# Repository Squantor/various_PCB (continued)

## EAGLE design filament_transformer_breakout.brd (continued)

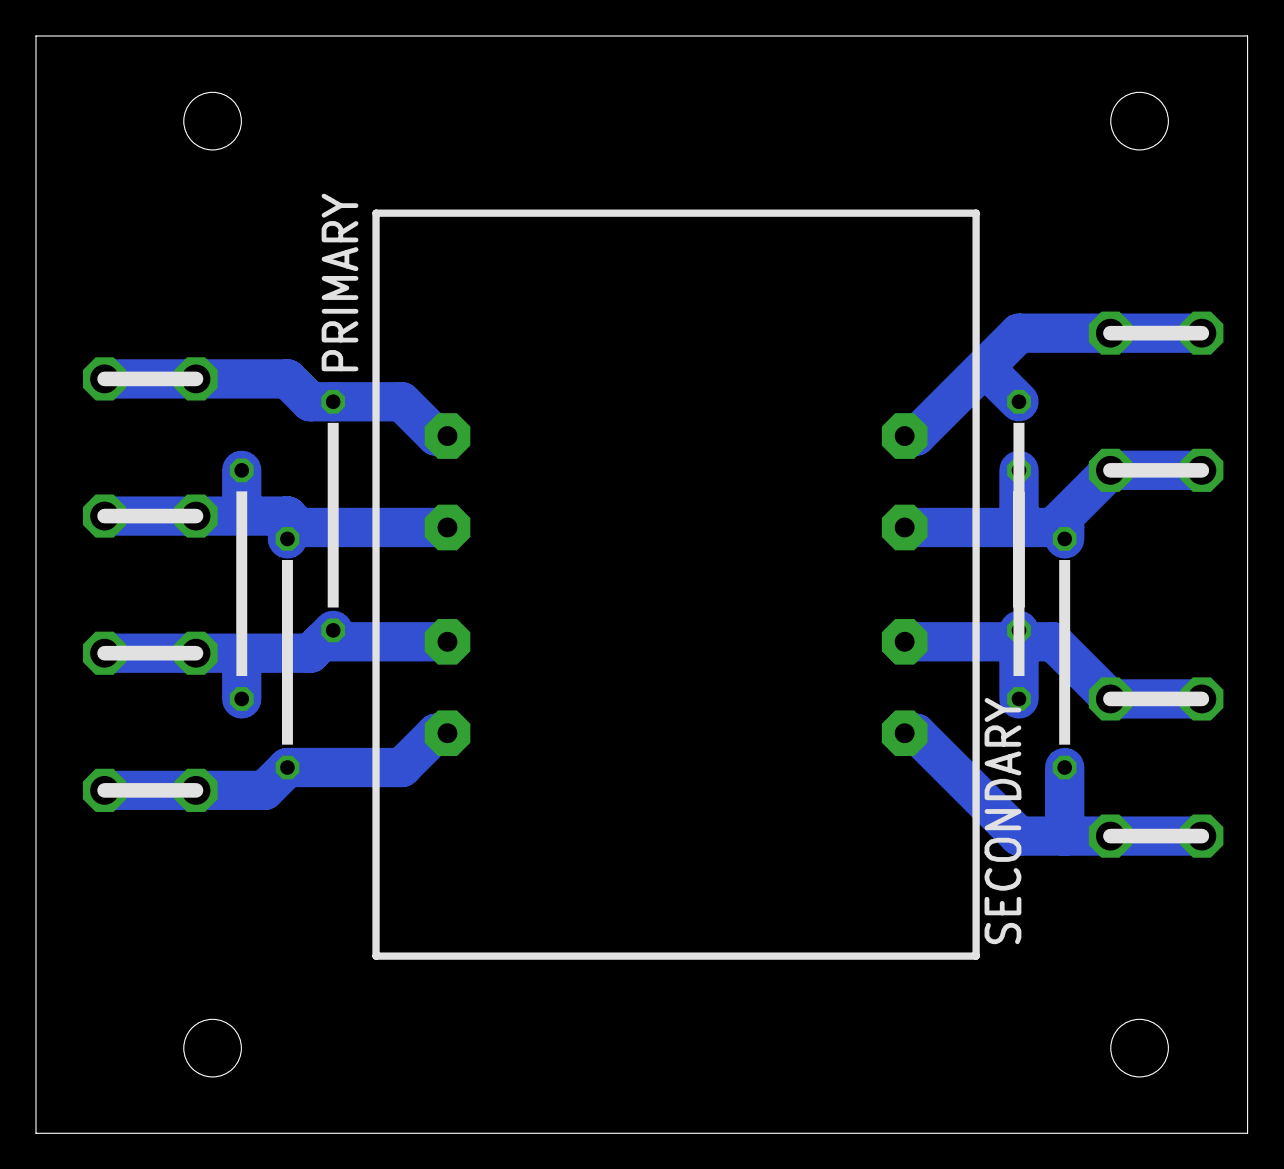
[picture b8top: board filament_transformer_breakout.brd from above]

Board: 2 copper layers, 67.3 x 61.0 mm, 15 parts (0 on the bottom side), 8 nets.

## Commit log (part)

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2021-03-21 forgot footprint definition for inductor
2021-03-21 placed and routed
2021-03-21 reviewed little logic SOT353 PCB
2021-03-21 reviewed SSR module
2021-04-01 WIP readme update
2021-04-01 further expanded readme and documentation
2021-04-01 fixed incorrect link to picture
2021-04-01 added frequencies to example table
2021-04-14 changed boostcap size, changed high current path to use multiple smaller vias
2021-04-16 different SSR's needed
2021-04-17 optimized placement of components to be more compact
2021-04-17 updated high power SSR with more compact components
2021-04-17 routed more compact components
2021-04-17 silk changes
2021-04-17 started with SY8291ABC breakout
2021-04-17 modified, layedout, and completed, now wait one day in between
2021-04-18 added additional current label, optimized some track placement
2021-04-18 added type of SSR label, fixed incorrect resistor value, updated versionnumber
2021-04-18 changed name of optotriac to generic name, the type field will tell what type of SSR it is
2021-04-18 updated versionnumber, changed optotriac name, added SSR type label, added cutouts near mounting holes and pins at potential
2021-04-19 updated versionnumber, removed one input capacitor, made design more compact, removed solder mask under IC for better cooling, added PCB title, changed Vout label
2021-04-19 updated versionnumber, fixed DRC errors
2021-04-19 added soldermask keepout, DRC errors fixed, title added, changed Vout Iout labels
2021-04-20 updated versionnumber, changed copper planes to have bigger spacing values, optimized ground planes a bit
2021-04-21 changed indicator power led, changed inductor size, enlarged PCB a bit
2021-04-22 updated versionnumber, changed coil sizes
2021-04-22 updated versionnumbers, added pin labels
2021-04-22 updated coil size, some component position optimizations
2021-04-23 changed some trace positions to have more distance from other potentials
2021-04-23 updated versionnumber, minor silk changes
2021-04-23 added current label, minor silk moves
2021-04-23 am forgot component labeling
2021-04-24 added picture of the CH340E module
2021-06-07 added initial USB-C PD only breakout
2021-06-07 updated with some USB-C connectors
2021-06-08 added LED indicator and breakout connector
2021-06-08 updated library with fixed USB-C PD connector
2021-06-08 ERC passed
2021-06-08 changed pin assignment on breakout to ease routing
2021-06-08 added additional 5mm led
2021-06-08 routed all the traces
2021-06-09 added on PCB USB-C connector
2021-06-09 changed LED series resistor to 0603
2021-06-09 copied over USB-C PD only breakout to new project
2021-06-09 changed USB-C connector
2021-06-10 minor copper changes, added pin labels
2021-06-10 added breakout, testpins, updated TODO's
2021-06-10 routed and silk placement completed
2021-06-10 started with CH340E with USB-C module
2021-06-10 placement fixed with on PCB USB-C breakout
2021-06-10 added regulator, changed resistor assignments
2021-06-11 created usb-C filter
2021-06-11 updated usb output schematic symbol
2021-06-12 updated versionnumber
2021-06-12 updated versionnumber, usb data lines routing improved, led position and test pads updated
2021-06-12 updated versionnumber, optimized differential pairs, silk placement improved
2021-06-12 updated todo, updated versionnumber
2021-06-12 silk and led position optimization
2021-06-12 seems that I actually worked on the CH340B USB breakout
2021-06-12 changed to CH340E and started routing/layout
2021-06-13 changed regulator to SOT23 lower cost regulator, updated versionnumber, put versionnumber and mechanical in seperate box
2021-06-13 added box
2021-06-13 routed SOT-23 regulator
2021-06-13 updated versionnumber, silk movement
2021-06-13 updated versionnumber, optimized some component placement
2021-06-13 updated versionnumber, added additional led to show usb output power, added jumper to separate the two power domains, changed led positioning
2021-06-13 renaming project names, seem they kept their origin project names!
2021-06-29 added USB-C breakout box 3d model as a copy from the hammond 1551M
2021-07-01 added USB-C hole to the box
2021-07-02 added opening for header connectors
2021-09-05 fixed usb A out schematic symbol
2021-09-05 updated versionnumber, fixed schematic component, some changes here and there on PCB
2021-09-05 bus link jumper to 0805 size due to higher currents
2021-09-05 routed and fixed error in board
2021-09-13 started sharp memory LCD breakout
2021-09-13 started with low power oscillator test
2021-09-13 initial schematic
2021-09-14 WIP schematic
2021-09-24 initial schematic with just connections
2021-09-24 started with inital layout
2021-09-25 added stabistor
2021-09-25 small changes
2021-09-26 added crystal footprint, passing ERC, updated versionnumber
2021-09-26 placing, routing, added decoupling capacitor, placing silk
2021-09-27 added TODO's
2021-09-27 added extra ground plane to PCB, added REG710 step up converter
2021-09-27 forgot resistor footprint
2021-09-28 changed regulator setup, updated versionnumber
2021-09-28 moved pinning of board, placed, and routed everything
2021-09-28 added extra ground testpoint near signal for easy measurements
2021-09-29 trying to add a TVS diode
2021-09-30 placed and routed TVS diode array, updated silk
2021-09-30 fixed mistake, missing resistor on DISP
2021-10-01 final checks before production
2021-10-01 final check before production
2021-10-12 minor silk changes
2021-10-12 updated version number and TODO
2021-10-12 few extra gnd vias
2021-10-12 changed one component value label to align better
2021-10-13 started with breakout for kailh choc buttons
2021-10-13 created keymatrix and initial placement
2021-10-15 modified keypad demo with simple pins
2021-10-15 added additional diode footprints
2021-10-15 routing completed, changed pinout to ease routing
2021-10-15 silk placement completed
2021-10-15 updated BOM
2021-10-15 started with 3 switch kailh breakout
2021-10-15 newer PCB library
2021-10-15 work in progress on schematic of 3 button kailh choc button breakout
2021-10-15 started with 4 switch kailh choc frontplate
2021-10-15 finished PCB
2021-10-15 copied 4 switch plate to 3 switch
2021-10-16 imported plate PCB to make sure we have the same dimensions
2021-10-16 routed and placed silk
2021-10-18 resizing PCB and different mounting method
2021-10-18 changed hole plate to smaller PCB so it can be tiled
2021-10-19 updated physical dimensions for 3 button choc frontplate
2021-10-19 moved connectors
2021-10-19 changed connector positions
2021-11-02 updated library
2021-11-03 place&route&silk position completed
2021-11-03 updated status
2021-11-07 schematic and routing completed
2021-11-07 renamed SOT363 breakout, as SOT is an abbreviation after all
2021-11-07 started with SOT457 breakout
2021-11-07 completed SOT457 breakout
2021-11-07 updated design status
2021-11-10 parking SOT666 breakout, not producable by oshpark
2021-11-10 moved some traces
2021-11-15 removed unproducable by oshpark project
2022-02-16 changed JST connectors to edge connectors, changed switch pitch
2022-02-16 updated 4 button breakout kailh switches
2022-03-22 added breakout for polulu 16 pin stepper motor driver
2022-03-22 further updates to breakout
2022-04-20 started with netfilter module
2022-04-21 assigned footprints from new PCB library
2022-04-21 added wurth library
2022-07-18 added test mainboard for a 10*10cm aluminium box
2022-07-18 added kicad6 ignorables
2022-07-18 inital mainboard test layout
2022-07-24 further connector placement
2022-07-25 further routing of busses, but blocked now
2022-08-29 updated footprints, silk placements
2022-09-16 alubox mainboard
2022-09-23 created board raspberry pi pico SWD breakout
2022-09-23 changed connector so we have silk space for versionnumber and date code
2022-09-23 updated to have power LED, silk placement, board layouted
2022-11-28 started with the SG1 strapubox template
2022-11-28 WIP schematic entry and component+footprint definitions
2022-11-29 WIP rectifier section
2022-11-30 WIP further development
2022-12-01 routing completed WIP silk placement
2023-02-11 updated cutout sizes
2023-02-11 added mounting hole definitions (forgot to add
2023-02-11 added small fixes, through wire holes
2023-04-09 redid board but with proper hole spacing and more flexible sizing
2023-04-09 fixed ERC errors
2023-04-10 WIP adding front LED and power switches
2023-04-11 further updates and additions to switch and leds
2023-04-14 place and route LED and switches
2023-04-15 fixed error with power switch pinout
2023-04-16 further routing
2023-04-17 updated pinouts
2023-04-18 routed new voltage rails
2023-05-05 started with alubox powersupply
2023-05-05 fixed board outline
2023-05-05 updated schematic with lessons learned
2023-05-05 forgot to save schematic
2023-05-05 minor positioning
2023-05-07 small outline adjustment to fit adapter box better
2023-05-13 added input switching connectors
2023-05-13 further changes of decoupling of AC inputs
2023-05-14 WIP PSU circuits
2023-05-19 further added PSU parts and fixed output regulator
2023-05-19 minor schematic fixes and errors
2023-05-19 further net shifts, changing component footprints to better fit
2023-05-19 WIP placing parts around regulators
2023-05-21 WIP component placement
2023-05-21 fixed power supply rail names
2023-05-23 Routing completed, WIP silk placement
2023-05-23 WIP silk placement
2023-05-27 reorganizing schematic
2023-05-27 added small regions for diodes to cool
2023-05-27 ERC passes, added powerflags
2023-05-27 fixed DRC errors
2023-05-28 changed jack connectors to use holed jacks
2023-05-28 minor optimizations
2023-05-28 placed and routed capacitors
2023-05-28 fixed small issue that aisler reported
2023-05-30 fixed aisler problems
2023-06-13 added 10x10 alubox drillguide
2023-06-19 added pin labels
2023-06-30 updated to kicad 7
2023-06-30 changed diode footprints, fixed LM337 footprint
2023-07-07 routing completed, placing silk
2023-07-16 Added electronics specific gitignore
2023-07-16 silk placement done, more optimizations on traces and cooling planes
2023-09-15 project changes
2023-09-15 updated drilling guide
2023-09-15 updated adapter and reviewed
2023-09-15 updated alubox PSU
2024-04-25 added white only neopixel sized led board
2024-05-24 added tiled PCB
2024-05-25 updated SOT457 breakout to kicad7 and added some parts
2024-05-26 panelized SOT457
2024-05-30 ready for production
2024-06-07 updated low power oscillator to kicad 7
2024-07-05 updated labels
2024-07-05 added WS2813 style LED
2024-07-05 removed old kailh switch breakouts
2024-07-05 started with small keypad test modules
2024-07-06 updated to newer kicad version
2024-07-08 changed/removed names
2024-07-08 fixing silk overlaps
2024-07-12 production run, updated versionnumbers, added tiled versions
2024-07-14 update to kicad 8
2024-07-16 minor updates
2024-07-17 small kicad 8 updates
2024-09-15 forgotten some data
2024-12-20 forgotten updates
2024-12-20 library update
2025-01-13 created SOT i2C EEPROM
2025-01-24 added EEPROM SOIC breakout
2025-01-24 updated and changed sharp memory lcd breakout
2025-03-23 preparation for production
2025-04-01 added tiled PCB's
2025-04-06 Work in progress CH224K USB-PD sink module
2025-05-02 updated parts things
2025-05-02 WIP ikea livecam LEDS mount
2025-05-02 added pick and place machine origin
2025-05-04 layout of LED's
2025-05-05 Place and route completed, WIP silk placement
2025-05-07 review and small changes
2025-05-11 review done of livecam
2025-06-01 added some documentation to IKEA webcam mount led ring
2025-07-29 fixed issues and simplified
2025-10-02 Added DIP CH221K breakout
2025-10-03 added SN6505 pushpull converter module
2025-10-04 renamed SN6505 module
2025-10-04 WIP VPS8701 module
2026-01-02 library update, silk labels added
2026-01-03 Added DIM module, simple SOT23 PMOS power switch
2026-01-04 small changes to CH221K with redundant components and adding labels
2026-01-04 changed label of CH221K power pin
2026-01-04 added SOIC-8 powergate
2026-01-08 fixing DRC/ERC warnings/errors
2026-01-09 renamed and cleaned up SN6505 breakout
2026-01-09 ERC/DRC fixed, small silk labels added
2026-01-09 Updated VPS8701 DIM, fixed ERC/DRC
2026-01-11 added new Power gate test PCB based on the ETA7014 powerswitch and protector
